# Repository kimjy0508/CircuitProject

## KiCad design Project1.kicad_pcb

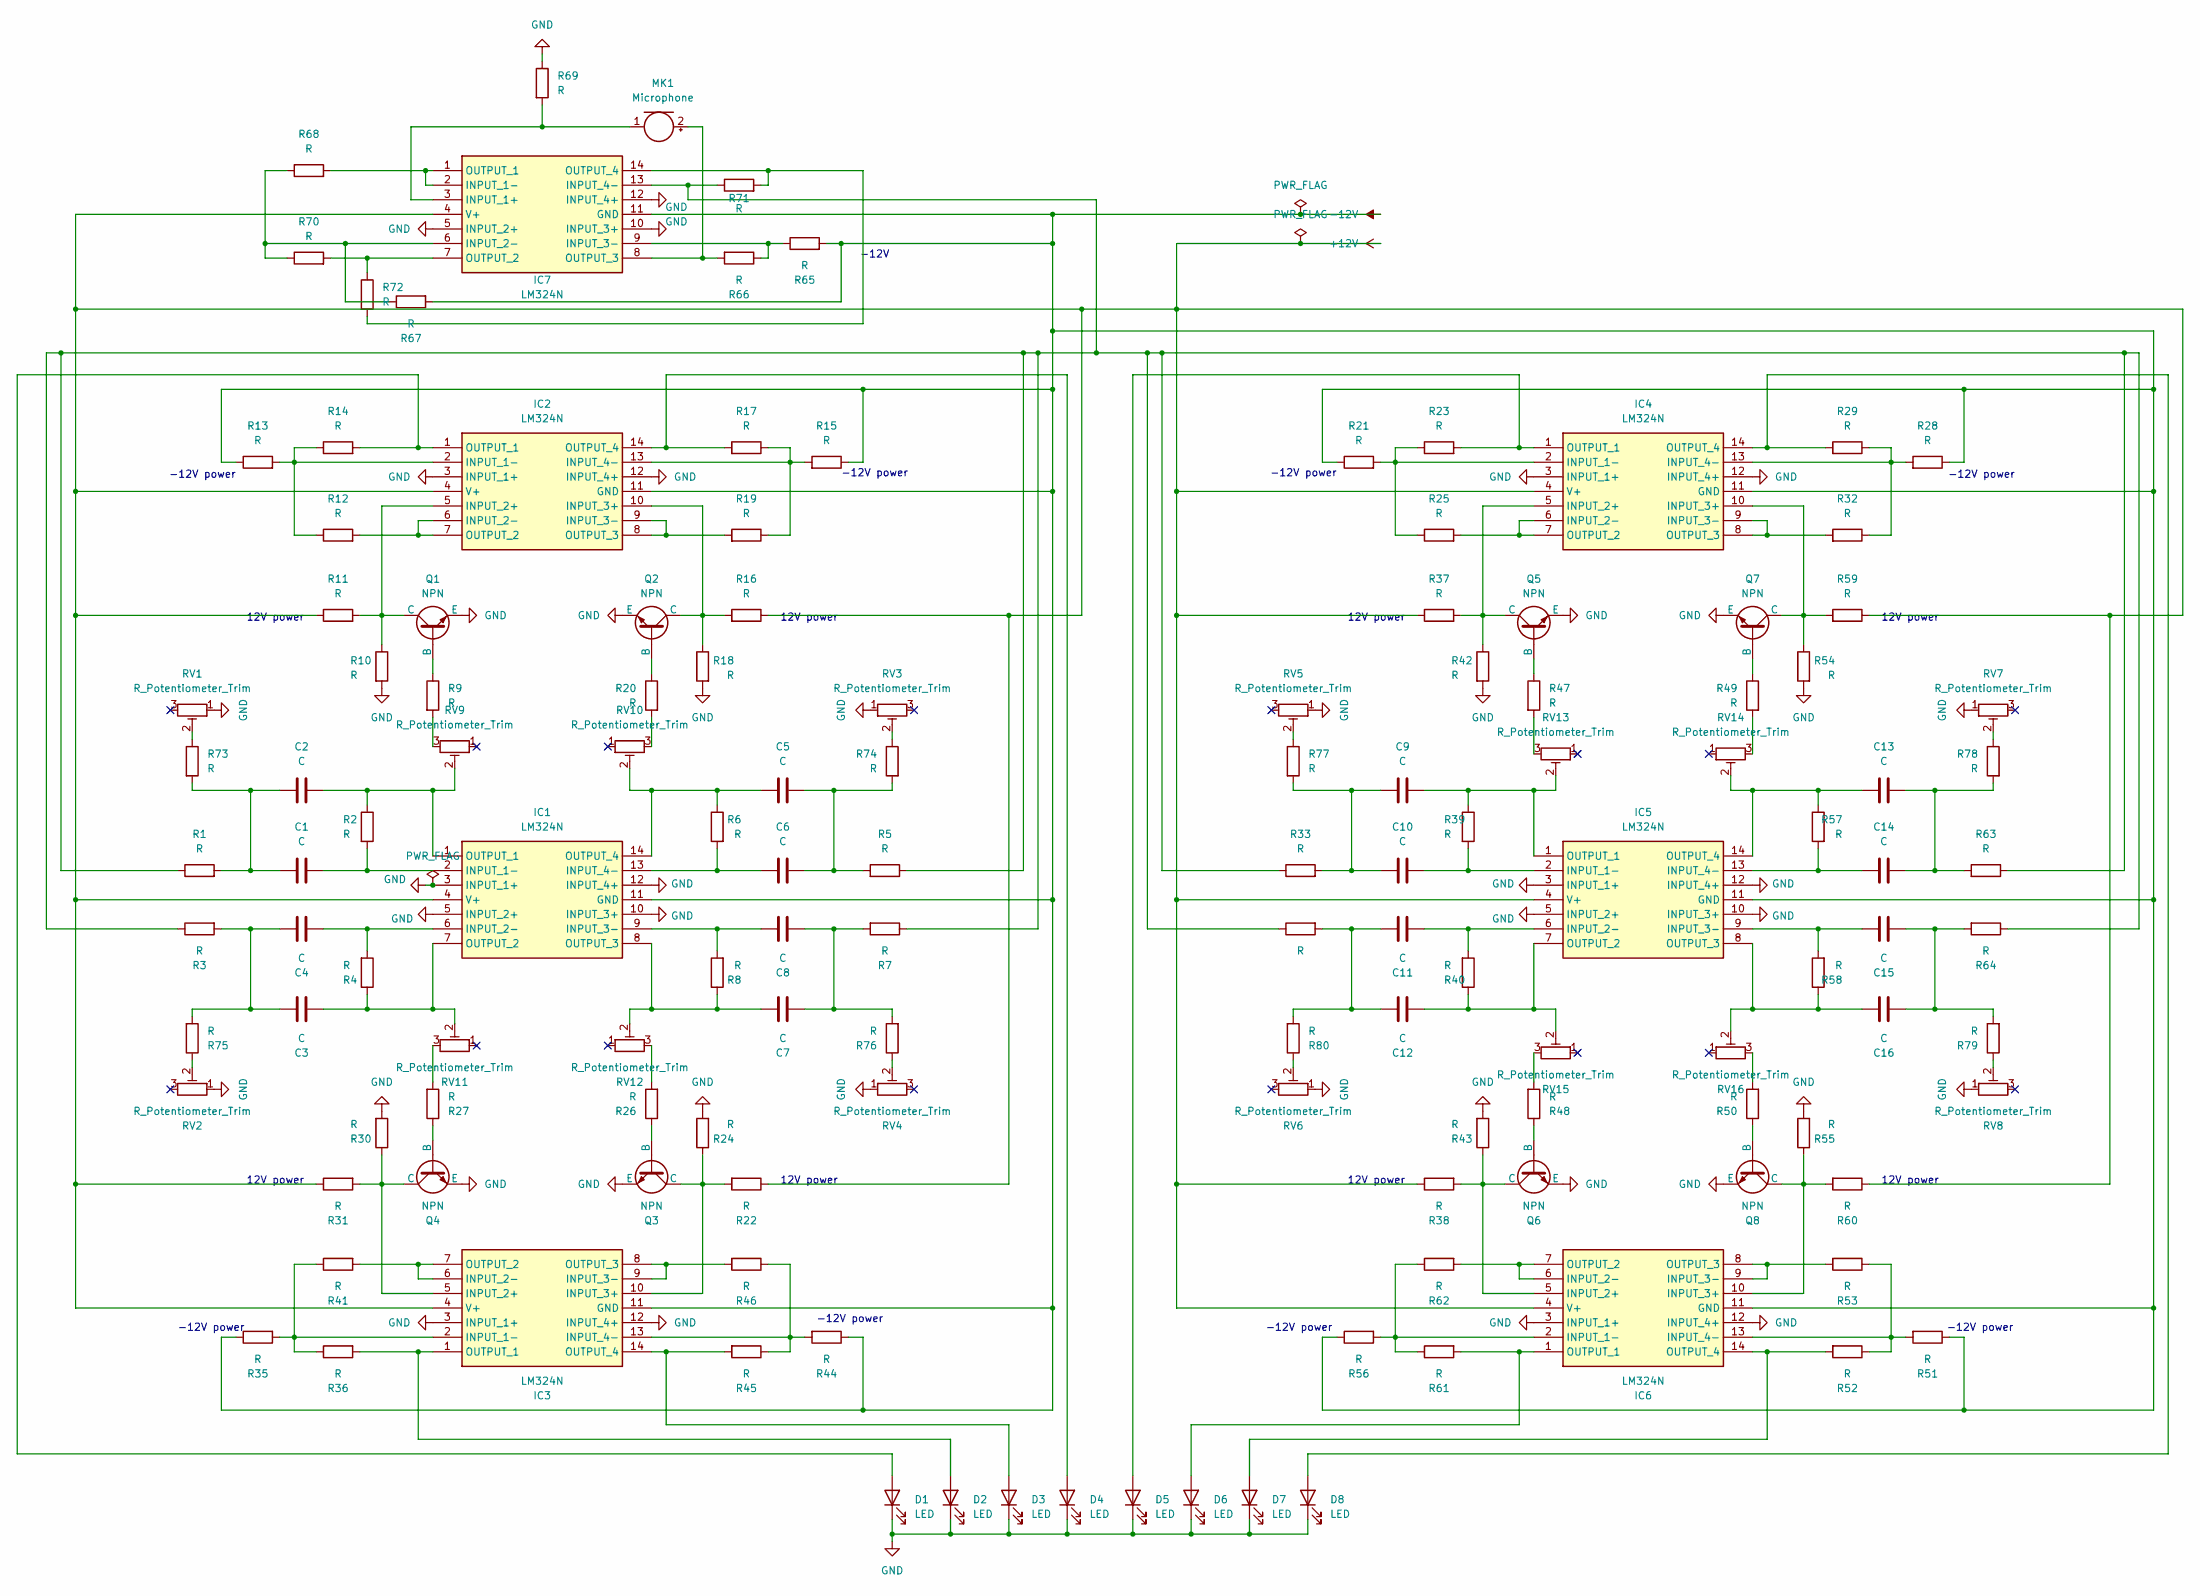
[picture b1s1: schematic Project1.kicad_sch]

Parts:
C1, C2, C3, C4, C5, C6, C7, C8, C9, C10, C11, C12, C13, C14, C15, C16: C; C_0201_0603Metric
D1, D2, D3, D4, D5, D6, D7, D8: LED; LED_D3.0mm
IC1, IC2, IC3, IC4, IC5, IC6, IC7: LM324N; Mouser Part Number 595-LM324N
MK1: Microphone; MIC_CMA-4544PF-W
Q1, Q2, Q3, Q4, Q5, Q6, Q7, Q8: NPN; TO-92_FAS_NPN
R1, R2, R3, R4, R5, R6, R7, R8, R9, R10, R11, R12, R13, R14, R15, R16, R17, R18, R19, R20, R21, R22, R23, R24, R25, R26, R27, R28, R29, R30, R31, R32, R33, R34, R35, R36, R37, R38, R39, R40, R41, R42, R43, R44, R45, R46, R47, R48, R49, R50, R51, R52, R53, R54, R55, R56, R57, R58, R59, R60, R61, R62, R63, R64, R65, R66, R67, R68, R69, R70, R71, R72, R73, R74, R75, R76, R77, R78, R79, R80: R; R_0201_0603Metric
RV1, RV2, RV3, RV4, RV5, RV6, RV7, RV8, RV9, RV10, RV11, RV12, RV13, RV14, RV15, RV16: R_Potentiometer_Trim; TRIM_TC33X-2-101E

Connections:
+12V: IC1.4 (V+), IC2.4 (V+), IC3.4 (V+), IC4.4 (V+), IC5.4 (V+), IC6.4 (V+), IC7.4 (V+), R11.1, R16.1, R22.1, R31.1, R37.1, R38.1, R59.1, R60.1
-12V: IC1.11 (GND), IC2.11 (GND), IC3.11 (GND), IC4.11 (GND), IC5.11 (GND), IC6.11 (GND), IC7.11 (GND), R13.1, R15.1, R21.1, R28.1, R35.1, R44.1, R51.1, R56.1, R65.2, R67.2
GND: D1.1 (K), D2.1 (K), D3.1 (K), D4.1 (K), D5.1 (K), D6.1 (K), D7.1 (K), D8.1 (K), IC1.3 (INPUT_1+), IC1.5 (INPUT_2+), IC1.10 (INPUT_3+), IC1.12 (INPUT_4+), IC2.3 (INPUT_1+), IC2.12 (INPUT_4+), IC3.3 (INPUT_1+), IC3.12 (INPUT_4+), IC4.3 (INPUT_1+), IC4.12 (INPUT_4+), IC5.3 (INPUT_1+), IC5.5 (INPUT_2+), IC5.10 (INPUT_3+), IC5.12 (INPUT_4+), IC6.3 (INPUT_1+), IC6.12 (INPUT_4+), IC7.5 (INPUT_2+), IC7.10 (INPUT_3+), IC7.12 (INPUT_4+), Q1.3 (E), Q2.3 (E), Q3.3 (E), Q4.3 (E), Q5.3 (E), Q6.3 (E), Q7.3 (E), Q8.3 (E), R10.2, R18.2, R24.2, R30.2, R42.2, R43.2, R54.2, R55.2, R69.1, RV1.1, RV2.1, RV3.1, RV4.1, RV5.1, RV6.1, RV7.1, RV8.1
unnamed: C1.1, C2.1, R1.2, R73.2
unnamed: C3.1, C4.1, R3.2, R75.2
unnamed: C5.1, C6.1, R5.2, R74.2
unnamed: C7.1, C8.1, R7.2, R76.2
unnamed: C9.1, C10.1, R33.2, R77.2
unnamed: C11.1, C12.1, R34.2, R80.2
unnamed: C13.1, C14.1, R63.2, R78.2
unnamed: C15.1, C16.1, R64.2, R79.2
unnamed: D1.2 (A), IC2.1 (OUTPUT_1), R14.2
unnamed: D2.2 (A), IC3.1 (OUTPUT_1), R36.2
unnamed: D3.2 (A), IC3.14 (OUTPUT_4), R45.2
unnamed: D4.2 (A), IC2.14 (OUTPUT_4), R17.2
unnamed: D5.2 (A), IC4.1 (OUTPUT_1), R23.2
unnamed: D6.2 (A), IC6.1 (OUTPUT_1), R61.2
unnamed: D7.2 (A), IC6.14 (OUTPUT_4), R52.2
unnamed: D8.2 (A), IC4.14 (OUTPUT_4), R29.2
unnamed: C1.2, IC1.2 (INPUT_1-), R2.2
unnamed: C4.2, IC1.6 (INPUT_2-), R4.2
unnamed: C8.2, IC1.9 (INPUT_3-), R8.2
unnamed: C6.2, IC1.13 (INPUT_4-), R6.2
unnamed: C2.2, IC1.1 (OUTPUT_1), R2.1, RV9.2
unnamed: C3.2, IC1.7 (OUTPUT_2), R4.1, RV11.2
unnamed: C7.2, IC1.8 (OUTPUT_3), R8.1, RV12.2
unnamed: C5.2, IC1.14 (OUTPUT_4), R6.1, RV10.2
unnamed: IC2.2 (INPUT_1-), R12.1, R13.2, R14.1
unnamed: IC2.5 (INPUT_2+), Q1.1 (C), R10.1, R11.2
unnamed: IC2.6 (INPUT_2-), IC2.7 (OUTPUT_2), R12.2
unnamed: IC2.10 (INPUT_3+), Q2.1 (C), R16.2, R18.1
unnamed: IC2.8 (OUTPUT_3), IC2.9 (INPUT_3-), R19.2
unnamed: IC2.13 (INPUT_4-), R15.2, R17.1, R19.1
unnamed: IC3.2 (INPUT_1-), R35.2, R36.1, R41.1
unnamed: IC3.5 (INPUT_2+), Q4.1 (C), R30.1, R31.2
unnamed: IC3.6 (INPUT_2-), IC3.7 (OUTPUT_2), R41.2
unnamed: IC3.10 (INPUT_3+), Q3.1 (C), R22.2, R24.1
unnamed: IC3.8 (OUTPUT_3), IC3.9 (INPUT_3-), R46.2
unnamed: IC3.13 (INPUT_4-), R44.2, R45.1, R46.1
unnamed: IC4.2 (INPUT_1-), R21.2, R23.1, R25.1
unnamed: IC4.5 (INPUT_2+), Q5.1 (C), R37.2, R42.1
unnamed: IC4.6 (INPUT_2-), IC4.7 (OUTPUT_2), R25.2
unnamed: IC4.10 (INPUT_3+), Q7.1 (C), R54.1, R59.2
unnamed: IC4.8 (OUTPUT_3), IC4.9 (INPUT_3-), R32.2
unnamed: IC4.13 (INPUT_4-), R28.2, R29.1, R32.1
unnamed: C10.2, IC5.2 (INPUT_1-), R39.2
unnamed: C11.2, IC5.6 (INPUT_2-), R40.2
unnamed: C15.2, IC5.9 (INPUT_3-), R58.2
unnamed: C14.2, IC5.13 (INPUT_4-), R57.2
unnamed: C9.2, IC5.1 (OUTPUT_1), R39.1, RV13.2
unnamed: C12.2, IC5.7 (OUTPUT_2), R40.1, RV15.2
unnamed: C16.2, IC5.8 (OUTPUT_3), R58.1, RV16.2
unnamed: C13.2, IC5.14 (OUTPUT_4), R57.1, RV14.2
unnamed: IC6.2 (INPUT_1-), R56.2, R61.1, R62.1
unnamed: IC6.5 (INPUT_2+), Q6.1 (C), R38.2, R43.1
unnamed: IC6.6 (INPUT_2-), IC6.7 (OUTPUT_2), R62.2
unnamed: IC6.10 (INPUT_3+), Q8.1 (C), R55.1, R60.2
unnamed: IC6.8 (OUTPUT_3), IC6.9 (INPUT_3-), R53.2
unnamed: IC6.13 (INPUT_4-), R51.2, R52.1, R53.1
unnamed: IC7.3 (INPUT_1+), MK1.1 (-), R69.2
unnamed: IC7.1 (OUTPUT_1), IC7.2 (INPUT_1-), R68.2
unnamed: IC7.6 (INPUT_2-), R67.1, R68.1, R70.1
unnamed: IC7.9 (INPUT_3-), R65.1, R66.1
unnamed: IC7.13 (INPUT_4-), R1.1, R3.1, R5.1, R7.1, R33.1, R34.1, R63.1, R64.1, R71.1
unnamed: IC7.7 (OUTPUT_2), R70.2, R72.1
unnamed: IC7.8 (OUTPUT_3), MK1.2 (+), R66.2
unnamed: IC7.14 (OUTPUT_4), R71.2, R72.2
unnamed: Q1.2 (B), R9.1
unnamed: Q2.2 (B), R20.1
unnamed: Q3.2 (B), R26.1
unnamed: Q4.2 (B), R27.1
unnamed: Q5.2 (B), R47.1
unnamed: Q6.2 (B), R48.1
unnamed: Q7.2 (B), R49.1
unnamed: Q8.2 (B), R50.1
unnamed: R9.2, RV9.3
unnamed: R20.2, RV10.3
unnamed: R26.2, RV12.3
unnamed: R27.2, RV11.3
unnamed: R47.2, RV13.3
unnamed: R48.2, RV15.3
unnamed: R49.2, RV14.3
unnamed: R50.2, RV16.3
unnamed: R73.1, RV1.2
unnamed: R74.1, RV3.2
unnamed: R75.1, RV2.2
unnamed: R76.1, RV4.2
unnamed: R77.1, RV5.2
unnamed: R78.1, RV7.2
unnamed: R79.1, RV8.2
unnamed: R80.1, RV6.2

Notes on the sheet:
12V power
-12V power
-12V

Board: 2 copper layers, 136 parts (0 on the bottom side), 91 nets, no tracks yet.

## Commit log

2025-05-18 0518_11:23 edited.
2025-05-18 0518 final edited.
2025-05-20 0520 Edited.
2025-05-23 0523 Edited.
2025-05-23 final.
2025-05-23 add some smd resistors
2025-05-26 거버파일까지 포함+조금 수정
